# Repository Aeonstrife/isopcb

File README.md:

# isopcb  

An OpenSource PCB for Ani's ISO macropad.  
Made for the Indian Mechanical Keyboard Community.

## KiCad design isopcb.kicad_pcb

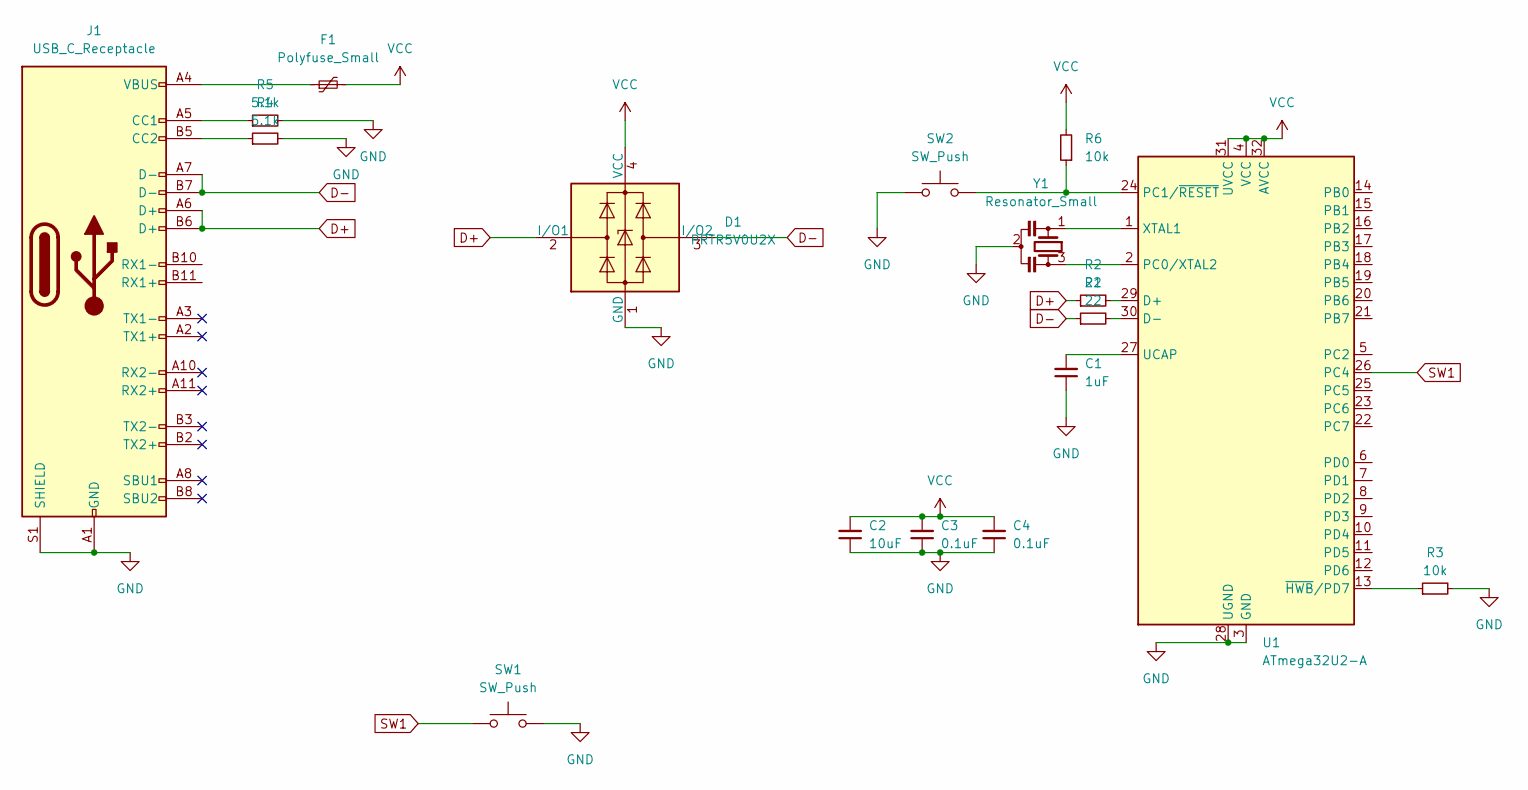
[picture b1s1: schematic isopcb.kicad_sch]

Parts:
C1: 1uF; C_0603_1608Metric
C2: 10uF; C_0603_1608Metric
C3, C4: 0.1uF; C_0603_1608Metric
D1: PRTR5V0U2X; SOT-143
F1: Polyfuse_Small; Fuse_0805_2012Metric
J1: USB_C_Receptacle; USB_C_Receptacle_HRO_TYPE-C-31-M-12
R1, R2: 22; R_0603_1608Metric
R3, R6: 10k; R_0603_1608Metric
R4, R5: 5.1k; R_0603_1608Metric
SW1: SW_Push; MX-Solderable-ISO
SW2: SW_Push; SW_SPST_TL3342
U1: ATmega32U2-A; TQFP-32_7x7mm_P0.8mm
Y1: Resonator_Small; Resonator_SMD_Murata_CSTxExxV-3Pin_3.0x1.1mm

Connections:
D+: D1.2 (I/O1), J1.A6 (D+), J1.B6 (D+), R2.1
D-: D1.3 (I/O2), J1.A7 (D-), J1.B7 (D-), R1.1
GND: C1.1, C2.1, C3.1, C4.1, D1.1 (GND), J1.A1 (GND), J1.A12 (GND), J1.B1 (GND), J1.B12 (GND), J1.S1 (SHIELD), R3.2, R4.2, R5.2, SW1.2, SW2.1, U1.3 (GND), U1.28 (UGND), Y1.2
unnamed: F1.1, J1.A4 (VBUS), J1.A9 (VBUS), J1.B4 (VBUS), J1.B9 (VBUS)
unnamed: J1.A5 (CC1), R5.1
unnamed: J1.B5 (CC2), R4.1
unnamed: R2.2, U1.29 (D+)
unnamed: R1.2, U1.30 (D-)
unnamed: U1.2 (PC0/XTAL2), Y1.3
unnamed: R6.1, SW2.2, U1.24 (PC1/~RESET)
unnamed: C1.2, U1.27 (UCAP)
unnamed: U1.1 (XTAL1), Y1.1
unnamed: R3.1, U1.13 (~HWB/PD7)
SW1: SW1.1, U1.26 (PC4)
VCC: C2.2, C3.2, C4.2, D1.4 (VCC), F1.2, R6.2, U1.4 (VCC), U1.31 (UVCC), U1.32 (AVCC)

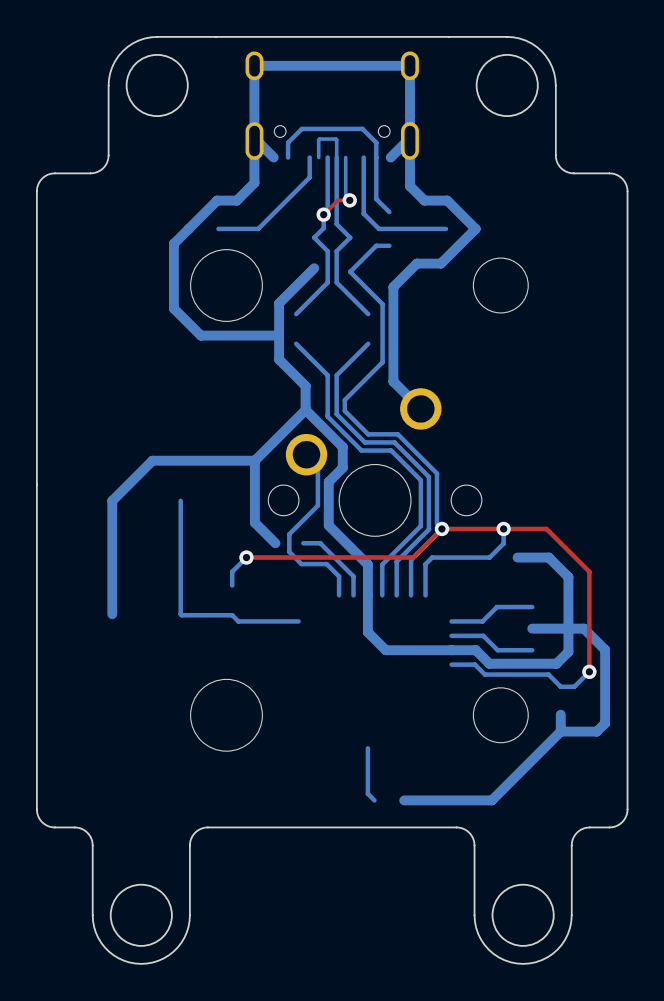
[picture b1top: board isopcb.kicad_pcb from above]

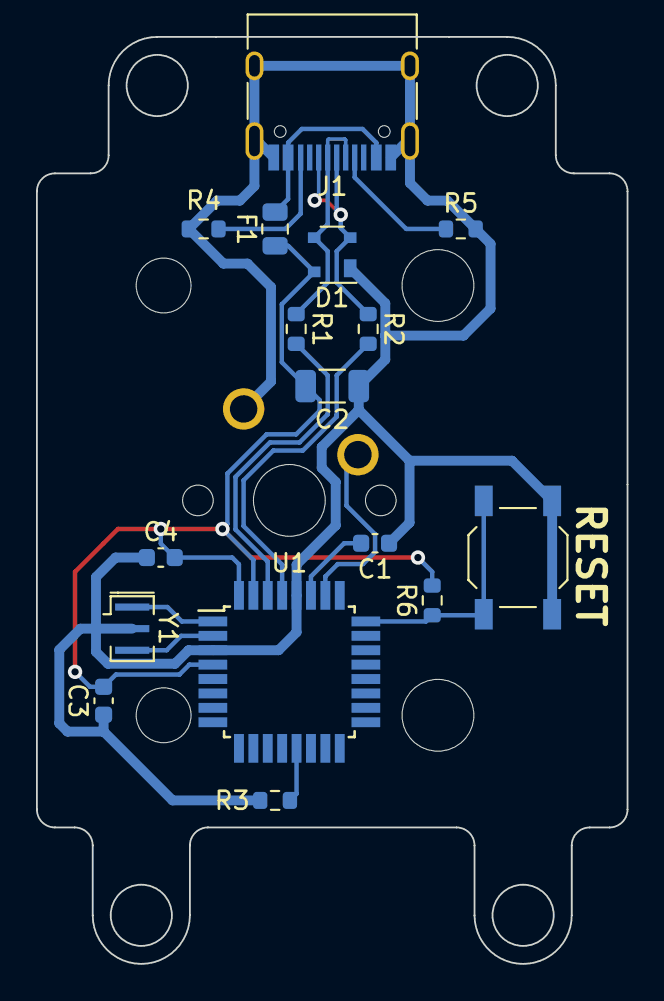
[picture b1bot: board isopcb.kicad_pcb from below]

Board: 2 copper layers, 32.8 x 51.5 mm, 17 parts (16 on the bottom side), 15 nets.

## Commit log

2025-02-15 Added files
